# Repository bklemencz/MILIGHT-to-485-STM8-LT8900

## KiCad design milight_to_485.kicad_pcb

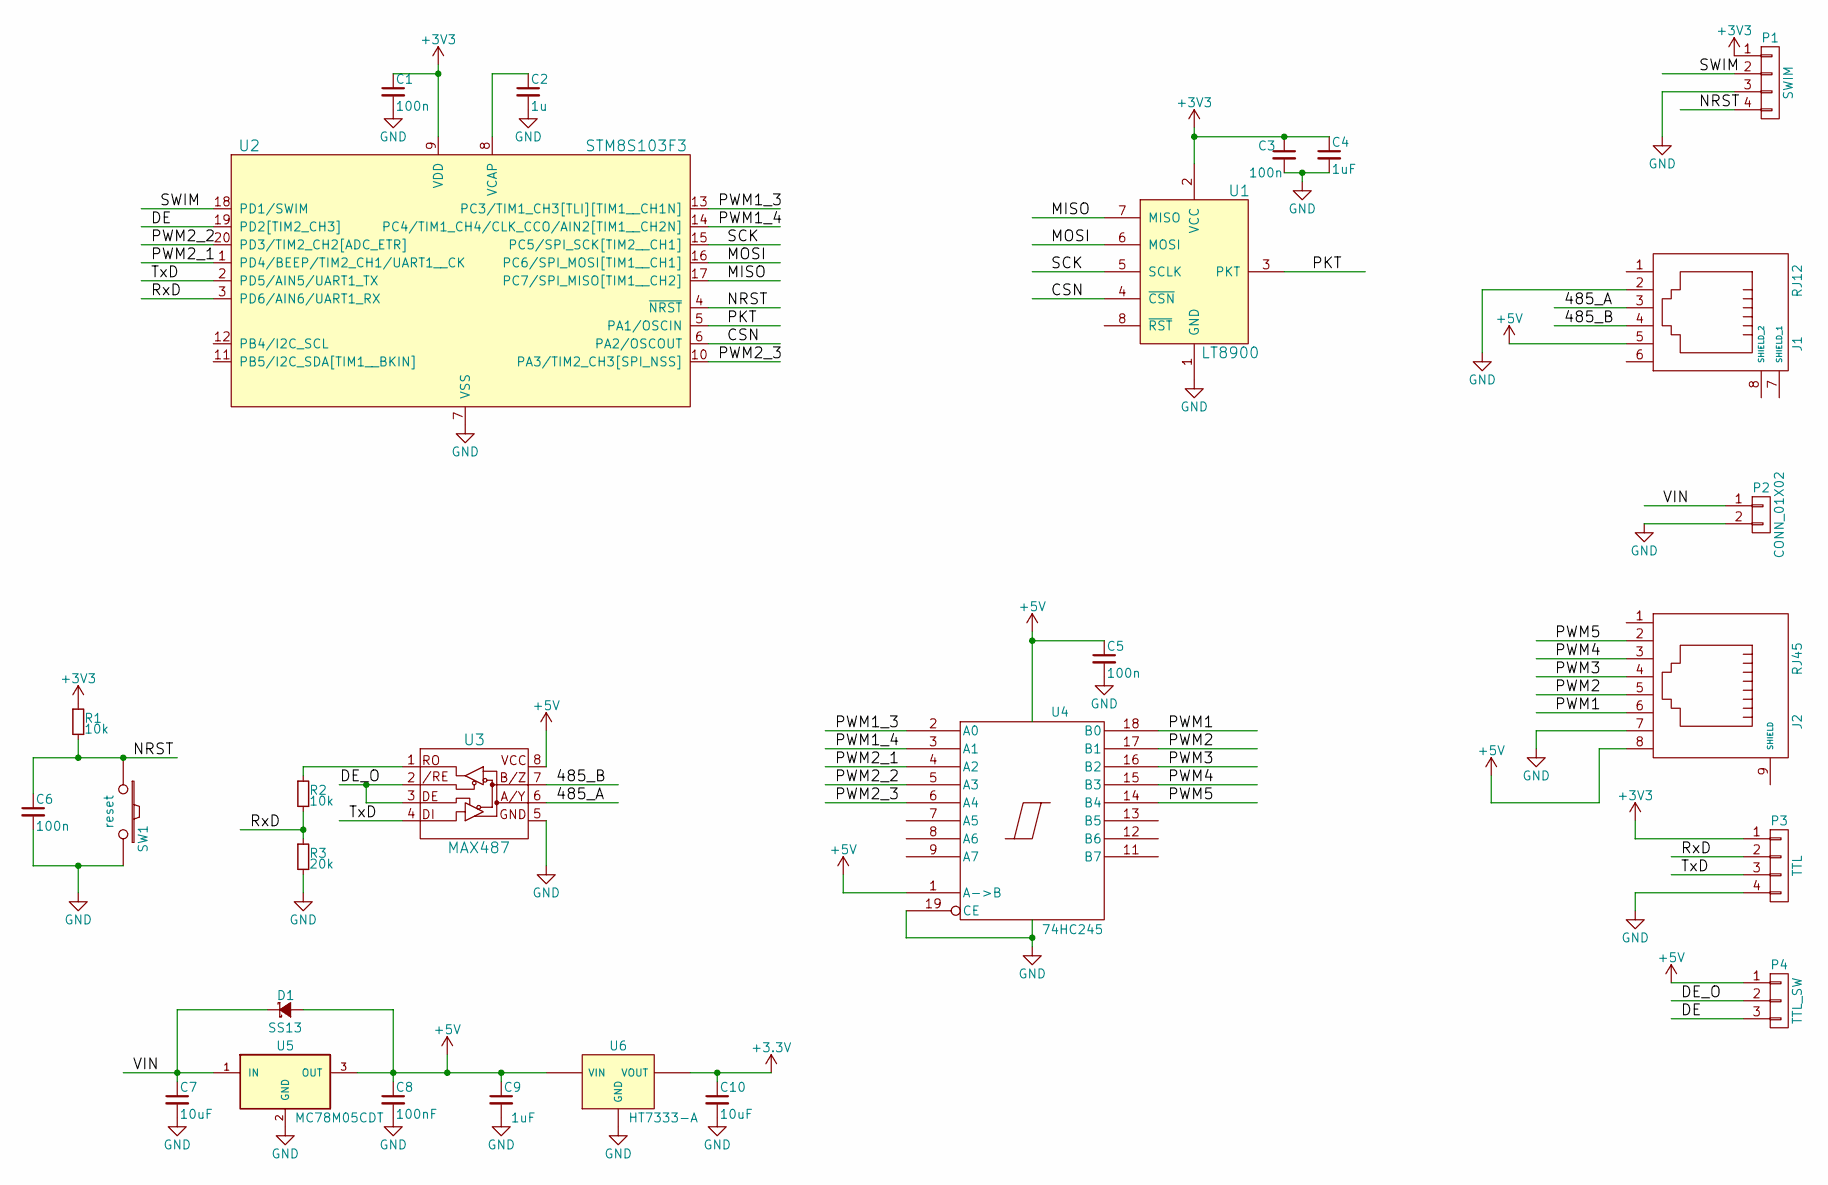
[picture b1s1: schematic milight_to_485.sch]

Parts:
C1, C3, C5, C6: 100n; C_0805
C2: 1u; C_0805
C4: 1uF; C_0805
C7, C10: 10uF; C_1206
C8: 100nF; C_0805
C9: 1uF; C_1206
D1: SS13; SMA_Standard
J1: RJ12; RJ12_2mm_Pitch
J2: RJ45; RJ45_UnShielded
P1: SWIM; Pin_Header_Straight_1x04
P2: CONN_01X02; Pin_Header_Straight_1x02
P3: TTL; Pin_Header_Straight_1x04
P4: TTL_SW; Pin_Header_Straight_1x03
R1, R2: 10k; R_0805
R3: 20k; R_0805
SW1: reset; SW_SPST_FSMSM
U1: LT8900; LT8900_2.54mmPitch_20x20
U2: STM8S103F3; SSOP-20_4.4x6.5mm_Pitch0.65mm
U3: MAX487; SOIC-8_3.9x4.9mm_Pitch1.27mm
U4: 74HC245; TSSOP-20_4.4x6.5mm_Pitch0.65mm
U5: MC78M05CDT; TO-252-2Lead
U6: HT7333-A; SOT89-3_Housing

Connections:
+5V: C5.1, C8.1, C9.1, D1.2 (A), J1.5, J2.8, P4.1, U3.8 (VCC), U4.1 (A->B), U4.20 (VCC), U5.3 (OUT), U6.2 (VIN)
/485_A: J1.3, U3.6 (A/Y)
/485_B: J1.4, U3.7 (B/Z)
/CSN: U1.4 (~CSN), U2.6 (PA2/OSCOUT)
/DE: P4.3, U2.19 (PD2[TIM2_CH3])
/DE_O: P4.2, U3.2 (/RE), U3.3 (DE)
/MISO: U1.7 (MISO), U2.17 (PC7/SPI_MISO[TIM1__CH2])
/MOSI: U1.6 (MOSI), U2.16 (PC6/SPI_MOSI[TIM1__CH1])
/NRST: C6.1, P1.4, R1.2, SW1.1, U2.4 (~NRST); also elsewhere on the board
/PKT: U1.3 (PKT), U2.5 (PA1/OSCIN)
/PWM1: J2.6, U4.18 (B0)
/PWM1_3: U2.13 (PC3/TIM1_CH3[TLI][TIM1__CH1N]), U4.2 (A0)
/PWM1_4: U2.14 (PC4/TIM1_CH4/CLK_CCO/AIN2[TIM1__CH2N]), U4.3 (A1)
/PWM2: J2.5, U4.17 (B1)
/PWM2_1: U2.1 (PD4/BEEP/TIM2_CH1/UART1__CK), U4.4 (A2)
/PWM2_2: U2.20 (PD3/TIM2_CH2[ADC_ETR]), U4.5 (A3)
/PWM2_3: U2.10 (PA3/TIM2_CH3[SPI_NSS]), U4.6 (A4)
/PWM3: J2.4, U4.16 (B2)
/PWM4: J2.3, U4.15 (B3)
/PWM5: J2.2, U4.14 (B4)
/RxD: P3.2, R2.2, R3.1, U2.3 (PD6/AIN6/UART1_RX)
/SCK: U1.5 (SCLK), U2.15 (PC5/SPI_SCK[TIM2__CH1])
/SWIM: P1.2, U2.18 (PD1/SWIM)
/TxD: P3.3, U2.2 (PD5/AIN5/UART1_TX), U3.4 (DI)
/VIN: C7.1, D1.1 (K), P2.1, U5.1 (IN)
GND: C1.2, C2.2, C3.2, C4.2, C5.2, C6.2, C7.2, C8.2, C9.2, C10.2, J1.2, J2.7, P1.3, P2.2, P3.4, R3.2, SW1.2, U1.1 (GND), U2.7 (VSS), U3.5 (GND), U4.10 (GND), U4.19 (CE), U5.2 (GND), U6.1 (GND); also elsewhere on the board
unnamed: C2.1, U2.8 (VCAP)
unnamed: R2.1, U3.1 (RO)

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
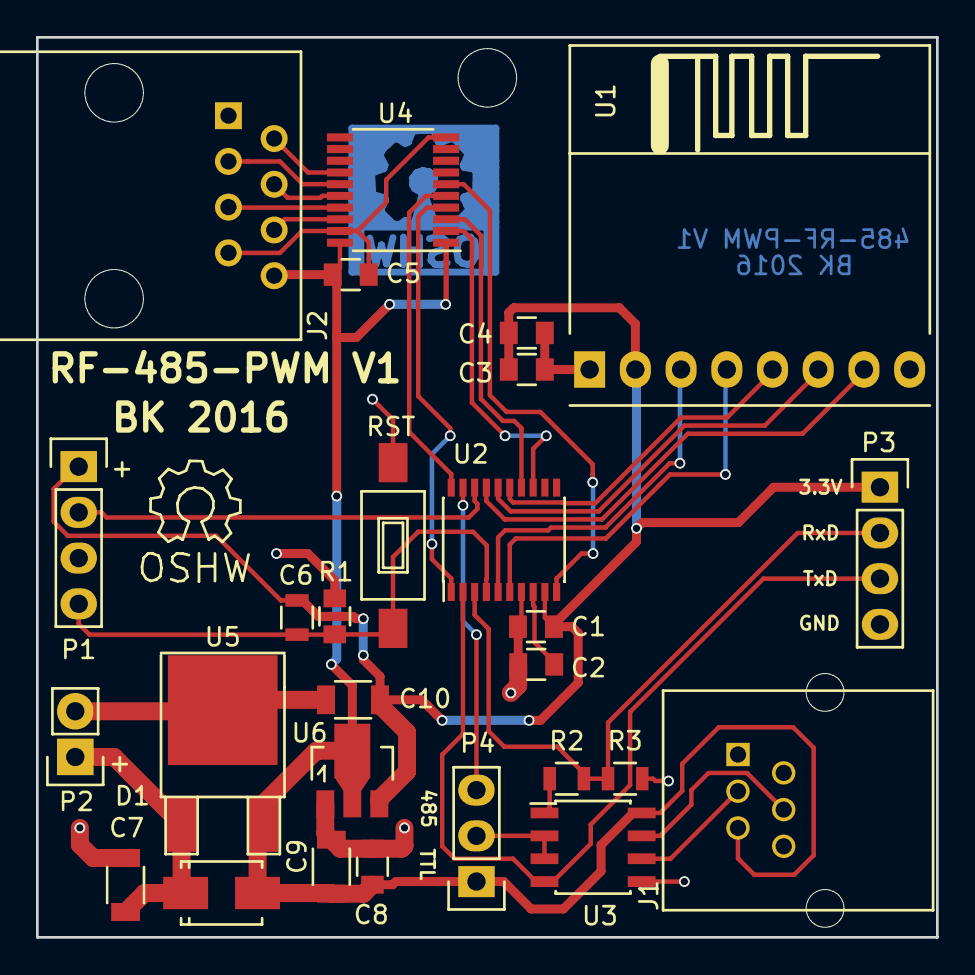
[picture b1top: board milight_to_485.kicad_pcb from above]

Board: 2 copper layers, 50.0 x 50.0 mm, 27 parts (0 on the bottom side), 29 nets.

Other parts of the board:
RST: reset; SW_SPST_TACT_SMD_3X6

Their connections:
/NRST: RST.1; also elsewhere on the board
GND: RST.2; also elsewhere on the board

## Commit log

2016-03-13 :octocat: Added .gitattributes & .gitignore files
2016-03-13 initial
2016-03-14 PCB upd
2016-03-14 PCB update
2016-03-15 PCB Update TTL Output Added
2016-03-15 Gerber Output
2016-03-15 small changes
2016-03-23 gerber
